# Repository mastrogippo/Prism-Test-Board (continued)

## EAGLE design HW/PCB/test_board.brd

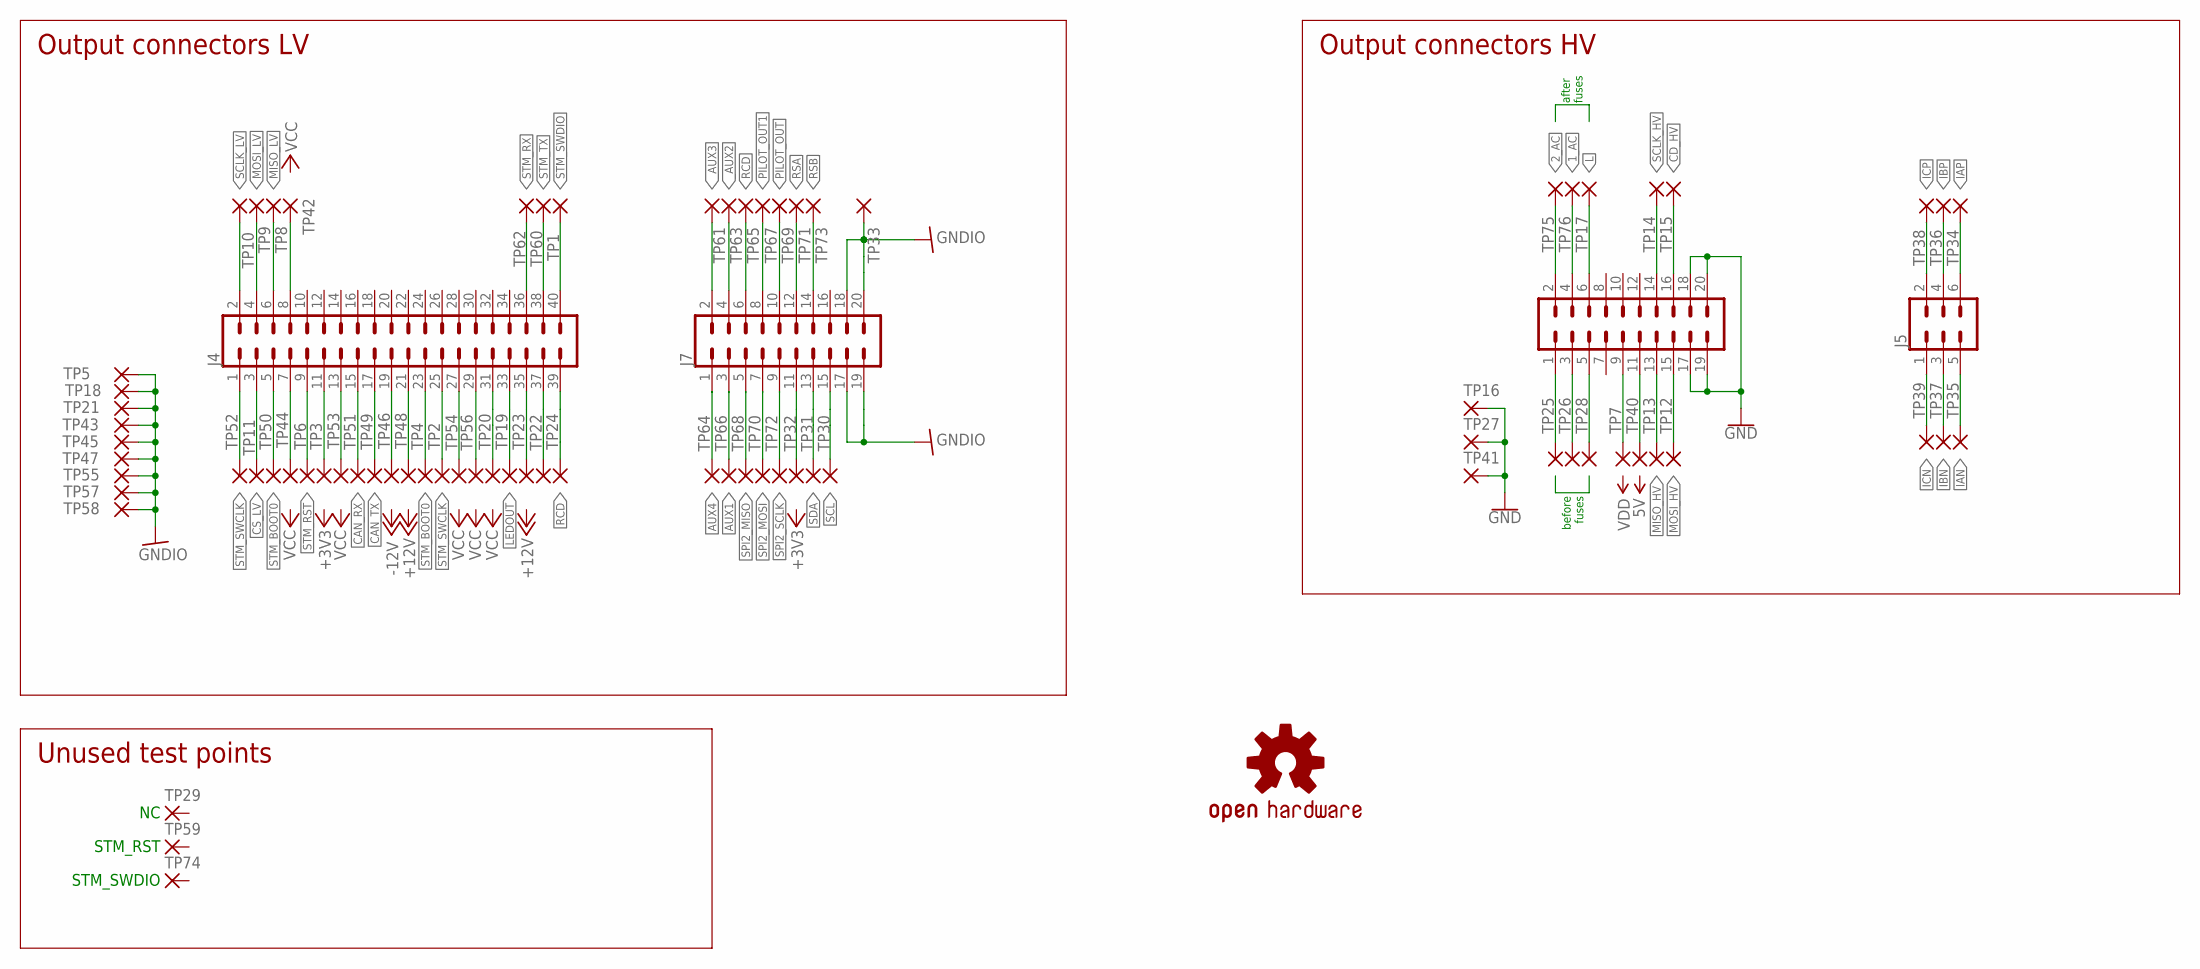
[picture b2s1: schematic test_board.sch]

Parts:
J4: CONN_20X2SHROUDED; 2X20_SHROUDED
J5: CONN_03X2SHROUD; 2X3-SHROUDED
J7, J8: CONN_10X2; 2X10
TP1, TP3, TP4, TP6, TP7, TP12, TP13, TP16, TP17, TP25, TP26, TP27, TP28, TP49, TP50, TP51, TP52, TP53, TP54, TP55, TP56, TP57, TP58, TP59, TP60, TP61, TP62, TP63, TP64, TP65, TP66, TP67, TP68, TP69, TP70, TP71, TP72, TP73, TP74, TP75, TP76: 1.35_HOLEROUND; 2,2/1,35_ROUND
TP2, TP8, TP9, TP10, TP14, TP15: 1.35_HOLEOFFSET; 1,7/1,35_OFFSET
TP5, TP11, TP18, TP19, TP20, TP21, TP22, TP23, TP24, TP29, TP30, TP31, TP32, TP33, TP34, TP35, TP36, TP37, TP38, TP39, TP40, TP41, TP42, TP43, TP44, TP45, TP46, TP47, TP48: 1.35_HOLELONG; 1,7/1,35_LONG
U$1: OSHW-LOGOL; OSHW-LOGO-L

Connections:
1_AC: J8.4, TP76.1
2_AC: J8.2, TP75.1
AUX1: J7.3, TP66.1
AUX4: J7.1, TP64.1
CAN_RX: J4.15, TP51.1
CAN_TX: J4.17, TP49.1
CD_HV: J8.16, TP15.1
CS_LV: J4.3, TP11.1
GND: J8.17, J8.18, J8.19, J8.20, TP16.1, TP27.1, TP41.1
GNDIO: J7.17, J7.18, J7.19, J7.20, TP5.1, TP18.1, TP21.1, TP33.1, TP43.1, TP45.1, TP47.1, TP55.1, TP57.1, TP58.1
IAN: J5.5, TP35.1
IAP: J5.6, TP34.1
IBN: J5.3, TP37.1
IBP: J5.4, TP36.1
ICN: J5.1, TP39.1
ICP: J5.2, TP38.1
L: J8.6, TP17.1
LEDOUT: J4.33, TP19.1
MISO_HV: J8.13, TP13.1
MISO_LV: J4.6, TP8.1
MOSI_HV: J8.15, TP12.1
MOSI_LV: J4.4, TP9.1
unnamed: J4.31, TP20.1
unnamed: J7.11, TP32.1
unnamed: J4.8, TP42.1
unnamed: J4.37, TP22.1
unnamed: J4.29, TP56.1
unnamed: J8.11, TP40.1
unnamed: J8.9, TP7.1
unnamed: J4.27, TP54.1
unnamed: J4.11, TP3.1
unnamed: J4.13, TP53.1
unnamed: J4.35, TP23.1
unnamed: J4.19, TP46.1
unnamed: J4.21, TP48.1
unnamed: J4.7, TP44.1
unnamed: J8.1, TP25.1
unnamed: J8.3, TP26.1
unnamed: J8.5, TP28.1
PILOT_OUT: J7.10, TP69.1
PILOT_OUT1: J7.8, TP67.1
RCD: J4.39, J7.6, TP24.1, TP65.1
RSA: J7.12, TP71.1
RSB: J7.14, TP73.1
SCL: J7.15, TP30.1
SCLK_HV: J8.14, TP14.1
SCLK_LV: J4.2, TP10.1
SDA: J7.13, TP31.1
SPI2_MISO: J7.5, TP68.1
SPI2_MOSI: J7.7, TP70.1
SPI2_SCLK: J7.9, TP72.1
STM_BOOT0: J4.5, J4.23, TP4.1, TP50.1
STM_RST: J4.9, TP6.1
STM_RX: J4.36, TP62.1
STM_SWCLK: J4.1, J4.25, TP2.1, TP52.1
STM_SWDIO: J4.40, TP1.1
STM_TX: J4.38, TP60.1
_AUX2: J7.4, TP63.1
_AUX3: J7.2, TP61.1

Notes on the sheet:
Output connectors LV
STM_SWDIO
STM_RST
Unused test points
Output connectors HV
after fuses
before fuses

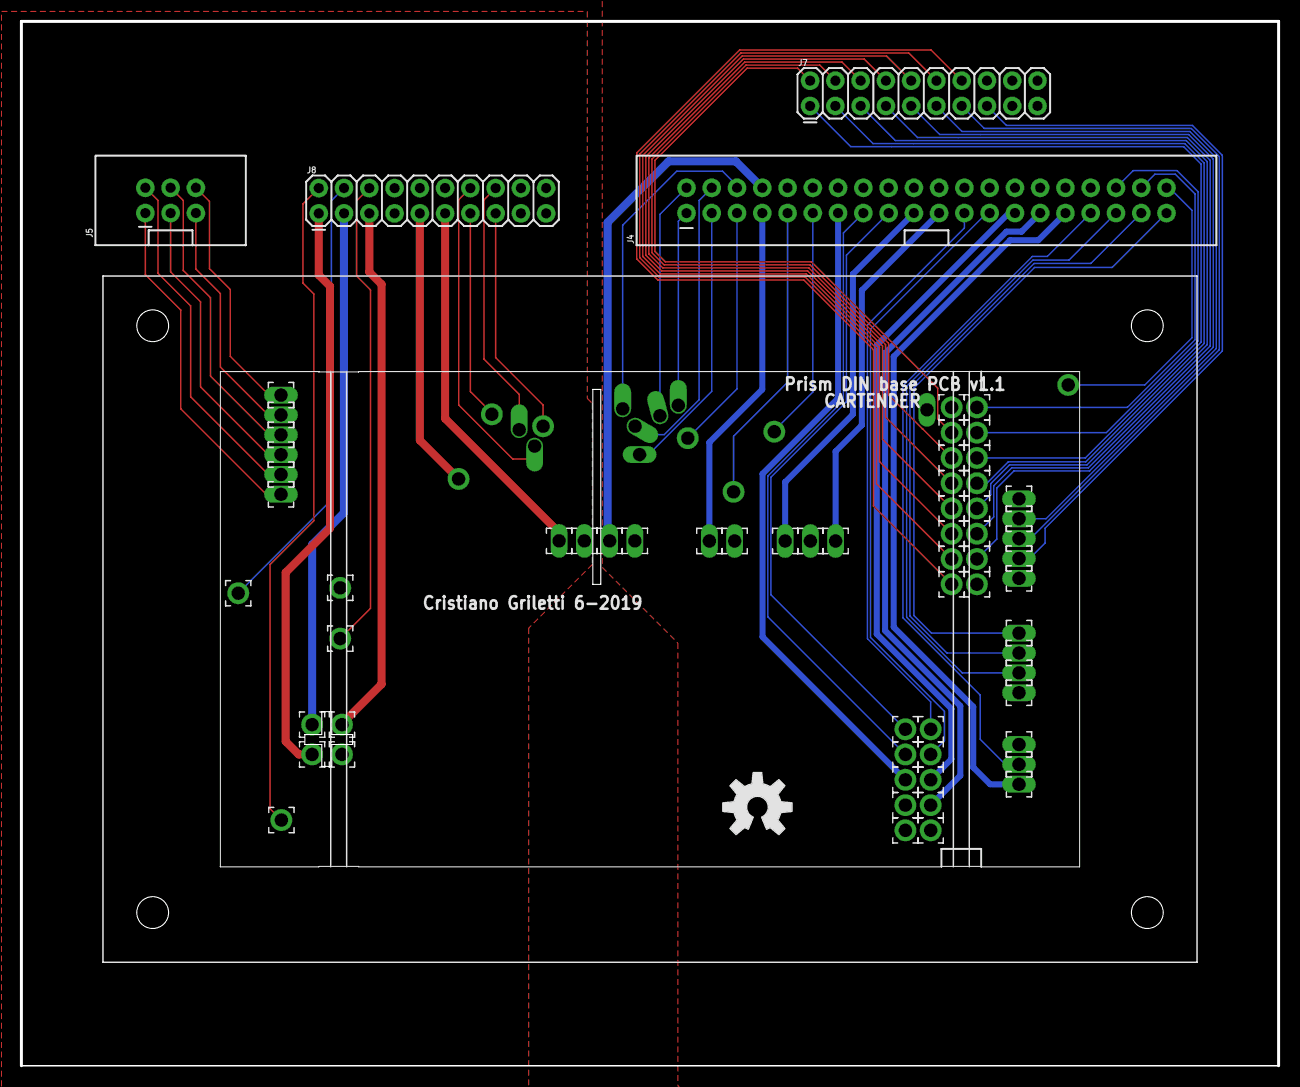
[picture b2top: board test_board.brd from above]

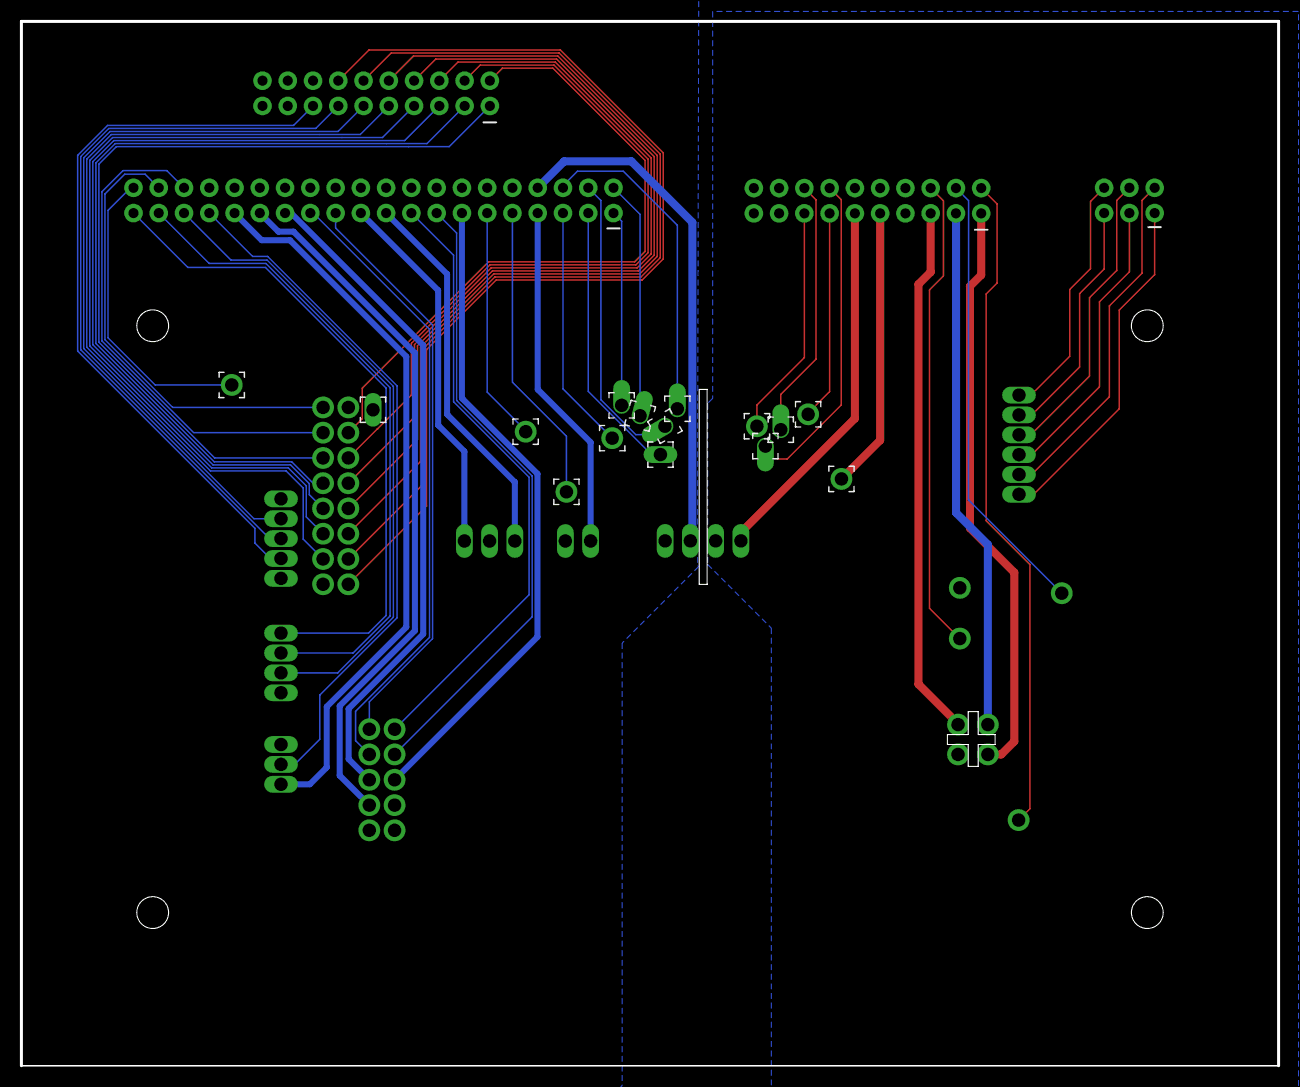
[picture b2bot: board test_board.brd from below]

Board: 2 copper layers, 126.4 x 105.0 mm, 81 parts (15 on the bottom side), 59 nets.

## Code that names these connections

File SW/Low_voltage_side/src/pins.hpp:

// Prism test board - LV side
// Copyright (C) 2019 Mastro Gippo
//
// This program is free software: you can redistribute it and/or modify it under
// the terms of the GNU General Public License as published by the Free Software
// Foundation, either version 3 of the License, or (at your option) any later
// version.
//
// This program is distributed in the hope that it will be useful, but WITHOUT
// ANY WARRANTY; without even the implied warranty of  MERCHANTABILITY or FITNESS
// FOR A PARTICULAR PURPOSE. See the GNU General Public License for more details.
//
// You should have received a copy of the GNU General Public License along with
// this program.  If not, see <http://www.gnu.org/licenses/>.

#ifndef PRISM_PINS_HPP
#define PRISM_PINS_HPP

#include <mbed.h>

// 5V relays
#define RELAY_5V_TEST_PIN PB_8  // relay for 5V line with 100ohm series resistor
#define RELAY_5V_PIN PB_9       // relay for 5V line with fuse

// Voltage sense lines
#define SENSE_3V3_PIN PA_0
#define SENSE_5V_PIN PA_1
#define SENSE_MIN_12V_PIN PB_0
#define SENSE_12V_PIN PB_1

// Current measure
#define CURR_MEAS_5V_PIN PA_2

// Pilot
#define PILOT_SENSE_PIN PA_5
#define PILOT1_SENSE_PIN PA_6

// Switch connected to resistors for emulating EV charging
#define EV_CHARGING_PIN PC_14
#define EV_CHARGING1_PIN PC_15

// AUX
#define AUX1_PIN PB_12
#define AUX2_PIN PA_11
#define AUX3_PIN PA_12
#define AUX4_PIN PA_8

// RCD
#define RCD_CTRL_PIN PA_7        // emulate RCD signal
#define RCD_TEST_SENSE_PIN PB_7  // read test request for RCD

// Communication
#define SWDIO_PIN PA_13
#define SWCLK_PIN PA_14

#define TX_PIN PA_9
#define RX_PIN PA_10

#define SDA_PIN PB_11
#define SCL_PIN PB_10

#define RSA_PIN PA_4
#define RSB_PIN PA_3

#define SCLK_PIN PB_13
#define MISO_PIN PB_14
#define MOSI_PIN PB_15

// Led
#define LEDOUT_SENSE_PIN PA_15

#endif
